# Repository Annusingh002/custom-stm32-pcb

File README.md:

# custom-stm32-pcb

## Overview

This project is a custom STM32 development board designed using KiCad. The board provides the essential hardware required to program and operate an STM32 microcontroller, making it suitable for embedded systems development and prototyping.

## Features

- Custom schematic designed in KiCad
- 2-layer PCB layout
- STM32 microcontroller
- 3.3 V power supply
- SWD programming interface
- Reset circuit
- Decoupling capacitors
- GPIO expansion headers
- Crystal oscillator 
- Power status LED 

## Software Used

- KiCad

## Hardware Components

| Component | Description |
|----------|-------------|
| STM32 MCU | Main microcontroller |
| Voltage Regulator | 3.3 V supply |
| Crystal Oscillator | System clock (if used) |
| Reset Button | Manual reset |
| SWD Header | Programming and debugging |
| LEDs | Status indication |

## Project Structure

```
custom-stm32-pcb/
│
├── Images/
├── KiCad/
├── Gerber/
└── README.md
```

## Design Checks

- ERC (Electrical Rules Check) completed
- DRC (Design Rules Check) completed
- Gerber files generated for PCB fabrication

##  Project Images

### Schematic

### PCB Layout

### 3D Top View

### 3D Bottom View

## Learning Outcomes

Through this project, I gained experience in:

- Schematic capture
- PCB layout and routing
- Component placement
- Power supply design
- Embedded hardware design
- Gerber file generation
- PCB design verification using ERC and DRC

## Future Improvements

- USB programming support
- On-board sensors
- Communication interfaces (UART, SPI, I2C)
- Power optimization

## Author

Annu

B.Tech in Electronics and Communication Engineering(AI/ML)
NSUT(DELHI)

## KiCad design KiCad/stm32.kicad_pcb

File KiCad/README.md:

This folder contains the KiCad project files for the STM32 Custom Development Board.

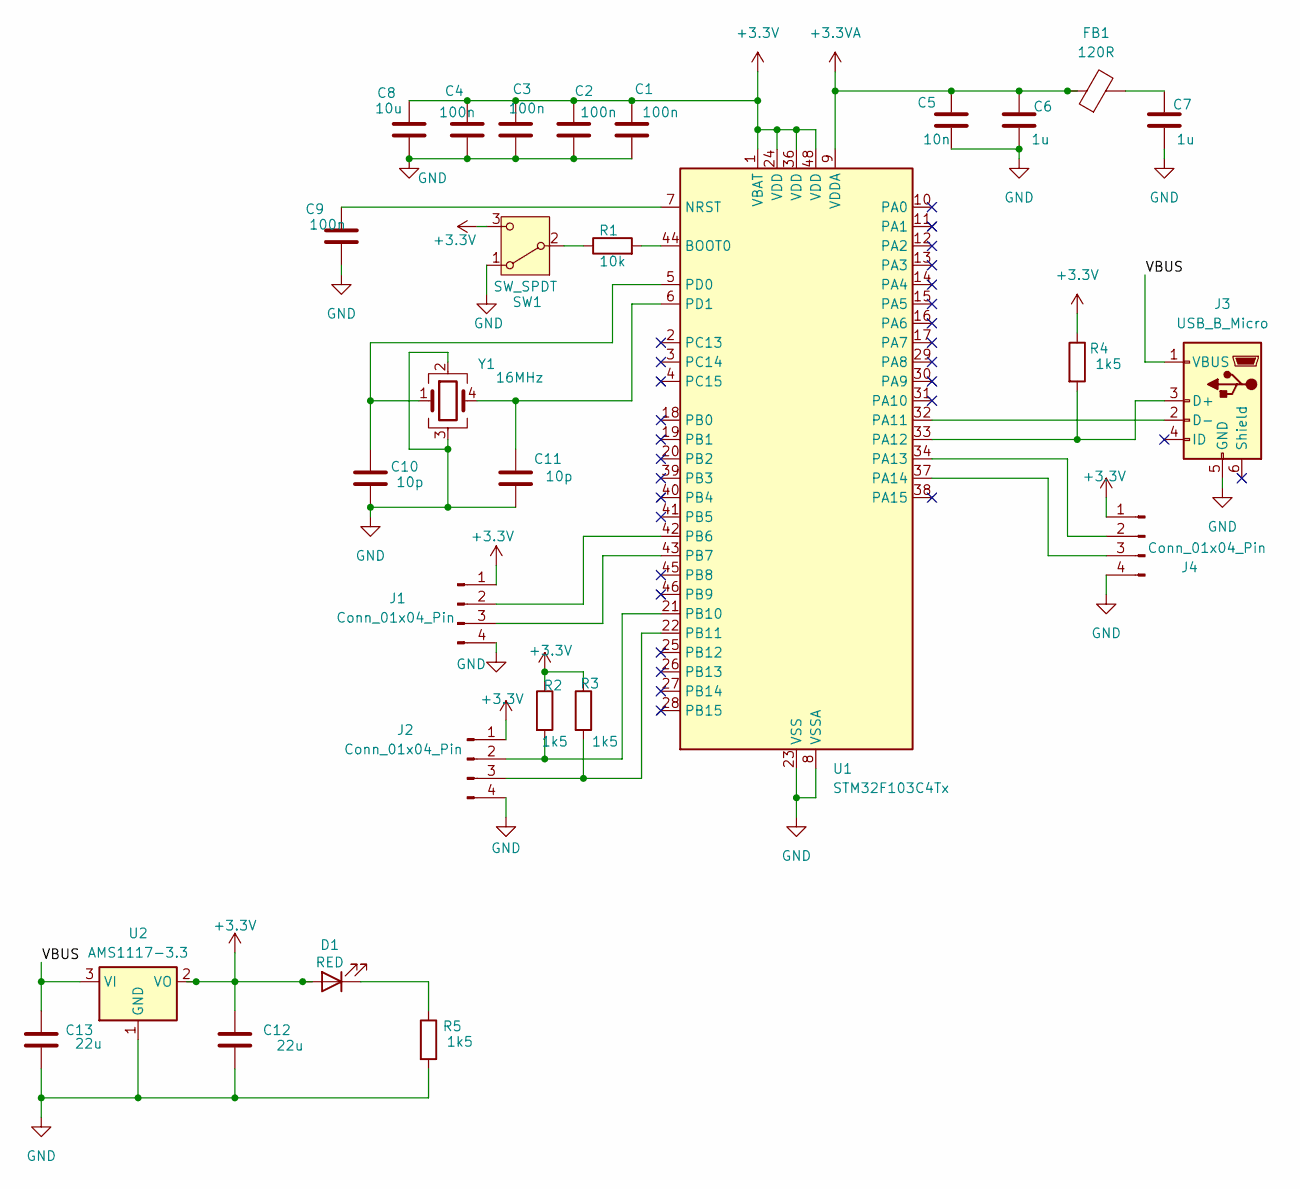
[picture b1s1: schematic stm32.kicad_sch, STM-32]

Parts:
C1, C2, C3, C4, C9: 100n; C_0402_1005Metric
C5: 10n; C_0603_1608Metric
C6, C7: 1u; C_0402_1005Metric
C8: 10u; C_0402_1005Metric
C10, C11: 10p; C_0402_1005Metric
C12, C13: 22u; C_0805_2012Metric
D1: RED; LED_0603_1608Metric
FB1: 120R; L_0603_1608Metric
J1, J2, J4: Conn_01x04_Pin; PinHeader_1x04_P2.54mm_Vertical
J3: USB_B_Micro; USB_Micro-B_Wuerth_629105150521
R1: 10k; R_0402_1005Metric
R2, R3, R4, R5: 1k5; R_0402_1005Metric
SW1: SW_SPDT; SW_Tactile_SPST_Angled_PTS645Vx39-2LFS
U1: STM32F103C4Tx; LQFP-48_7x7mm_P0.5mm
U2: AMS1117-3.3; SOT-223-3_TabPin2
Y1: 16MHz; Crystal_SMD_3225-4Pin_3.2x2.5mm

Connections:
+3.3V: C1.1, C2.1, C3.1, C4.1, C8.1, C12.1, D1.2 (A), J1.1, J2.1, J4.1, R2.1, R3.1, R4.1, SW1.3 (C), U1.1 (VBAT), U1.24 (VDD), U1.36 (VDD), U1.48 (VDD), U2.2 (VO)
+3.3VA: C5.1, C6.1, FB1.1, U1.9 (VDDA)
/VBUS: C13.1, J3.1 (VBUS), U2.3 (VI)
GND: C1.2, C2.2, C3.2, C4.2, C5.2, C6.2, C7.2, C8.2, C9.2, C10.2, C11.2, C12.2, C13.2, J1.4, J2.4, J3.5 (GND), J4.4, R5.2, SW1.1 (A), U1.8 (VSSA), U1.23 (VSS), U1.35 (VSS), U1.47 (VSS), U2.1 (GND), Y1.2, Y1.3
unnamed: C7.1, FB1.2
unnamed: D1.1 (K), R5.1
unnamed: J1.2, U1.42 (PB6)
unnamed: J1.3, U1.43 (PB7)
unnamed: J2.2, R2.2, U1.21 (PB10)
unnamed: J2.3, R3.2, U1.22 (PB11)
unnamed: J3.3 (D+), R4.2, U1.33 (PA12)
unnamed: J3.2 (D-), U1.32 (PA11)
unnamed: J4.2, U1.34 (PA13)
unnamed: J4.3, U1.37 (PA14)
unnamed: R1.1, SW1.2 (B)
unnamed: R1.2, U1.44 (BOOT0)
unnamed: C9.1, U1.7 (NRST)
unnamed: C10.1, U1.5 (PD0), Y1.1
unnamed: C11.1, U1.6 (PD1), Y1.4

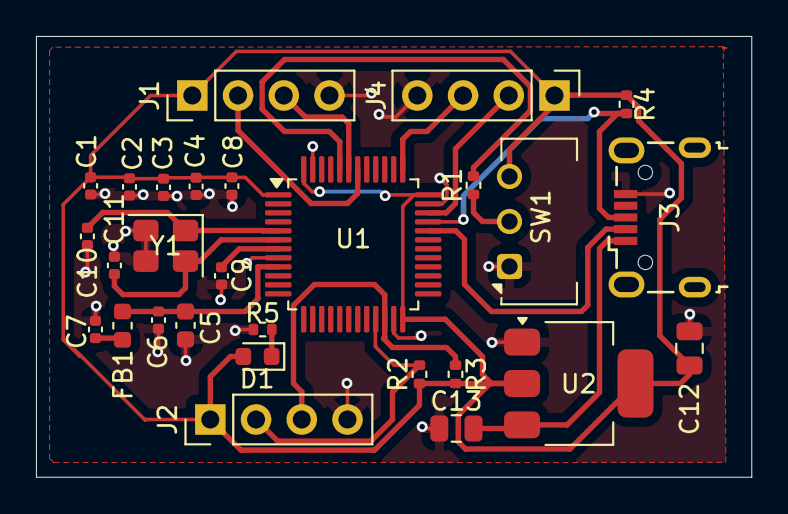
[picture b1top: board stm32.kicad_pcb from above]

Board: 2 copper layers, 39.7 x 24.5 mm, 28 parts (0 on the bottom side), 19 nets.
